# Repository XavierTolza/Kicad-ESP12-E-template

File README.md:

# About

This is a simple template for kicad to get started making ESP12-E based boards.

# Installation

Juste clone the repository in `$HOME/kicad/template/esp12E`:

```
git clone https://github.com/XavierTolza/Kicad-ESP12-E-template.git $HOME/kicad/template/esp12E
```

And start a new project from the template

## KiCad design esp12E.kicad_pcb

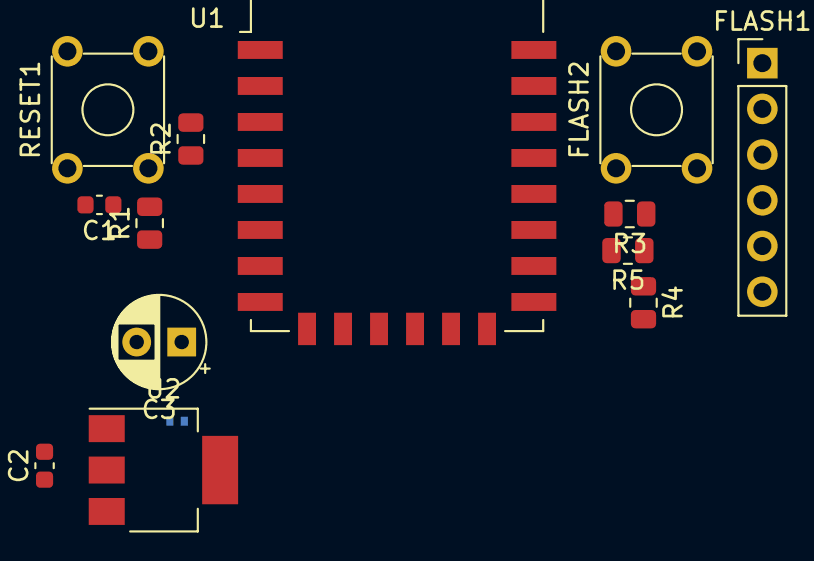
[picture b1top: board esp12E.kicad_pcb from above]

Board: 2 copper layers, 14 parts (1 on the bottom side), 11 nets, no tracks yet.

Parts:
C1: C; C_0603_1608Metric
C2: 10uF; C_0603_1608Metric
C3: 22uF; CP_Radial_D5.0mm_P2.50mm
FLASH1: Conn_01x06; PinHeader_1x06_P2.54mm_Vertical
FLASH2: SW_MEC_5E; SW_TH_Tactile_Omron_B3F-10xx
JP1: SolderJumper_3_Bridged12; SolderJumper-3_P1.3mm_Bridged2Bar12_RoundedPad1.0x1.5mm
R1, R2, R3, R4, R5: 10k; R_0805_2012Metric
RESET1: SW_MEC_5E; SW_TH_Tactile_Omron_B3F-10xx
U1: ESP-12E
U2: AMS1117-3.3; SOT-223-3_TabPin2

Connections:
+3V3: C3.1, JP1.1, R1.1, R2.1, R3.1, R5.1, U1.8, U2.2
/ESP_EN: R2.2, U1.3
/ESP_RESET: C1.1, R1.2, RESET1.3, RESET1.4, U1.1
/FLASH_RX: FLASH1.2, U1.22
/FLASH_TX: FLASH1.3, U1.21
/FLASH_VCC: FLASH1.4, JP1.2
/GPIO0: FLASH2.1, FLASH2.2, R3.2, U1.18
/GPIO2: R5.2, U1.17
/GPIO15: R4.1, U1.16
/Vin: C2.1, JP1.3, U2.3
GND: C1.2, C2.2, C3.2, FLASH1.6, FLASH2.3, FLASH2.4, R4.2, RESET1.1, RESET1.2, U1.15, U2.1
